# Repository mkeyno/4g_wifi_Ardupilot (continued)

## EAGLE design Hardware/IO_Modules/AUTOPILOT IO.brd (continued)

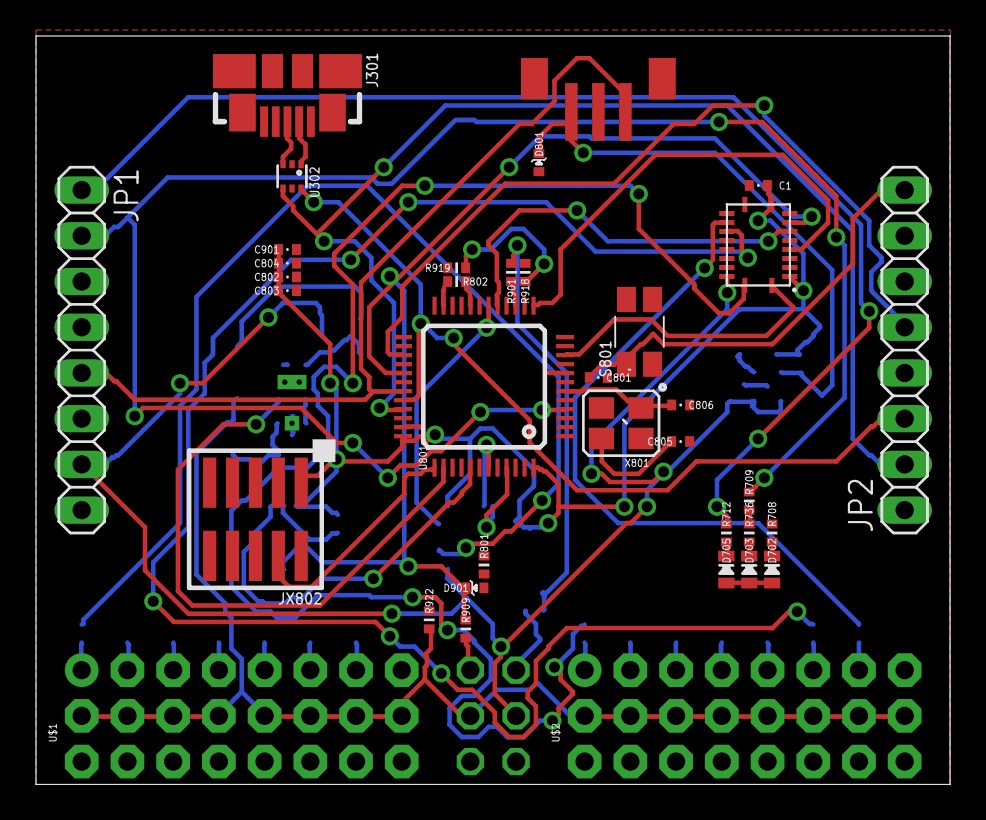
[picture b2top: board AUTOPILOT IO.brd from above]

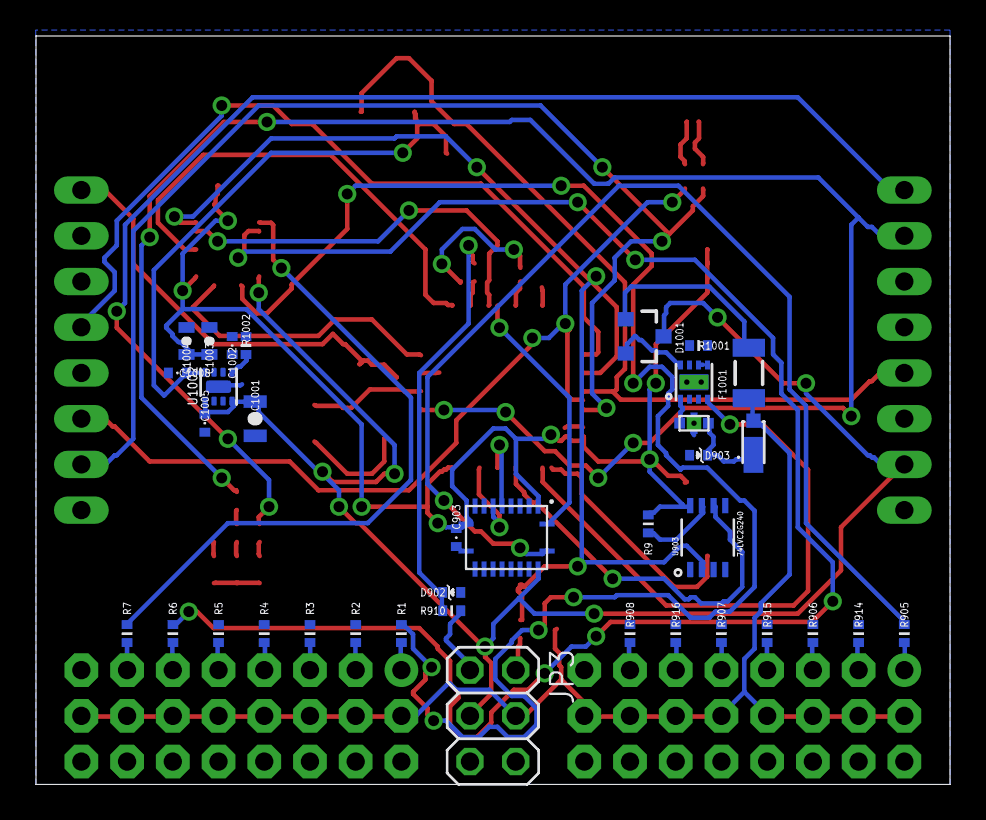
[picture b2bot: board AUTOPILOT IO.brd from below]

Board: 2 copper layers, 50.8 x 41.6 mm, 72 parts (36 on the bottom side), 91 nets.

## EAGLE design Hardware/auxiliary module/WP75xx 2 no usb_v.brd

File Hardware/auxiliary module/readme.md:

Airprime WPx5xx-76xx series is a Multiple-core embedded Linux system which used as  auxiliary core system that can provide secondary & backup IMU data, GPS data, advance terrain navigation , 4G video streaming and any hardware management for enhancing drone capabilities

## Specification  ##

In this 2 layer design following peripheral has been break out 
- 1 sync  Serial port
- 1 SPI(slave) 
- 1 I2C port
- 1 mini sim card slut 
- 1 USB 2.1 port
- 1 SD mini card slut 
- 4 analog pin

size of board is 7x5 cm

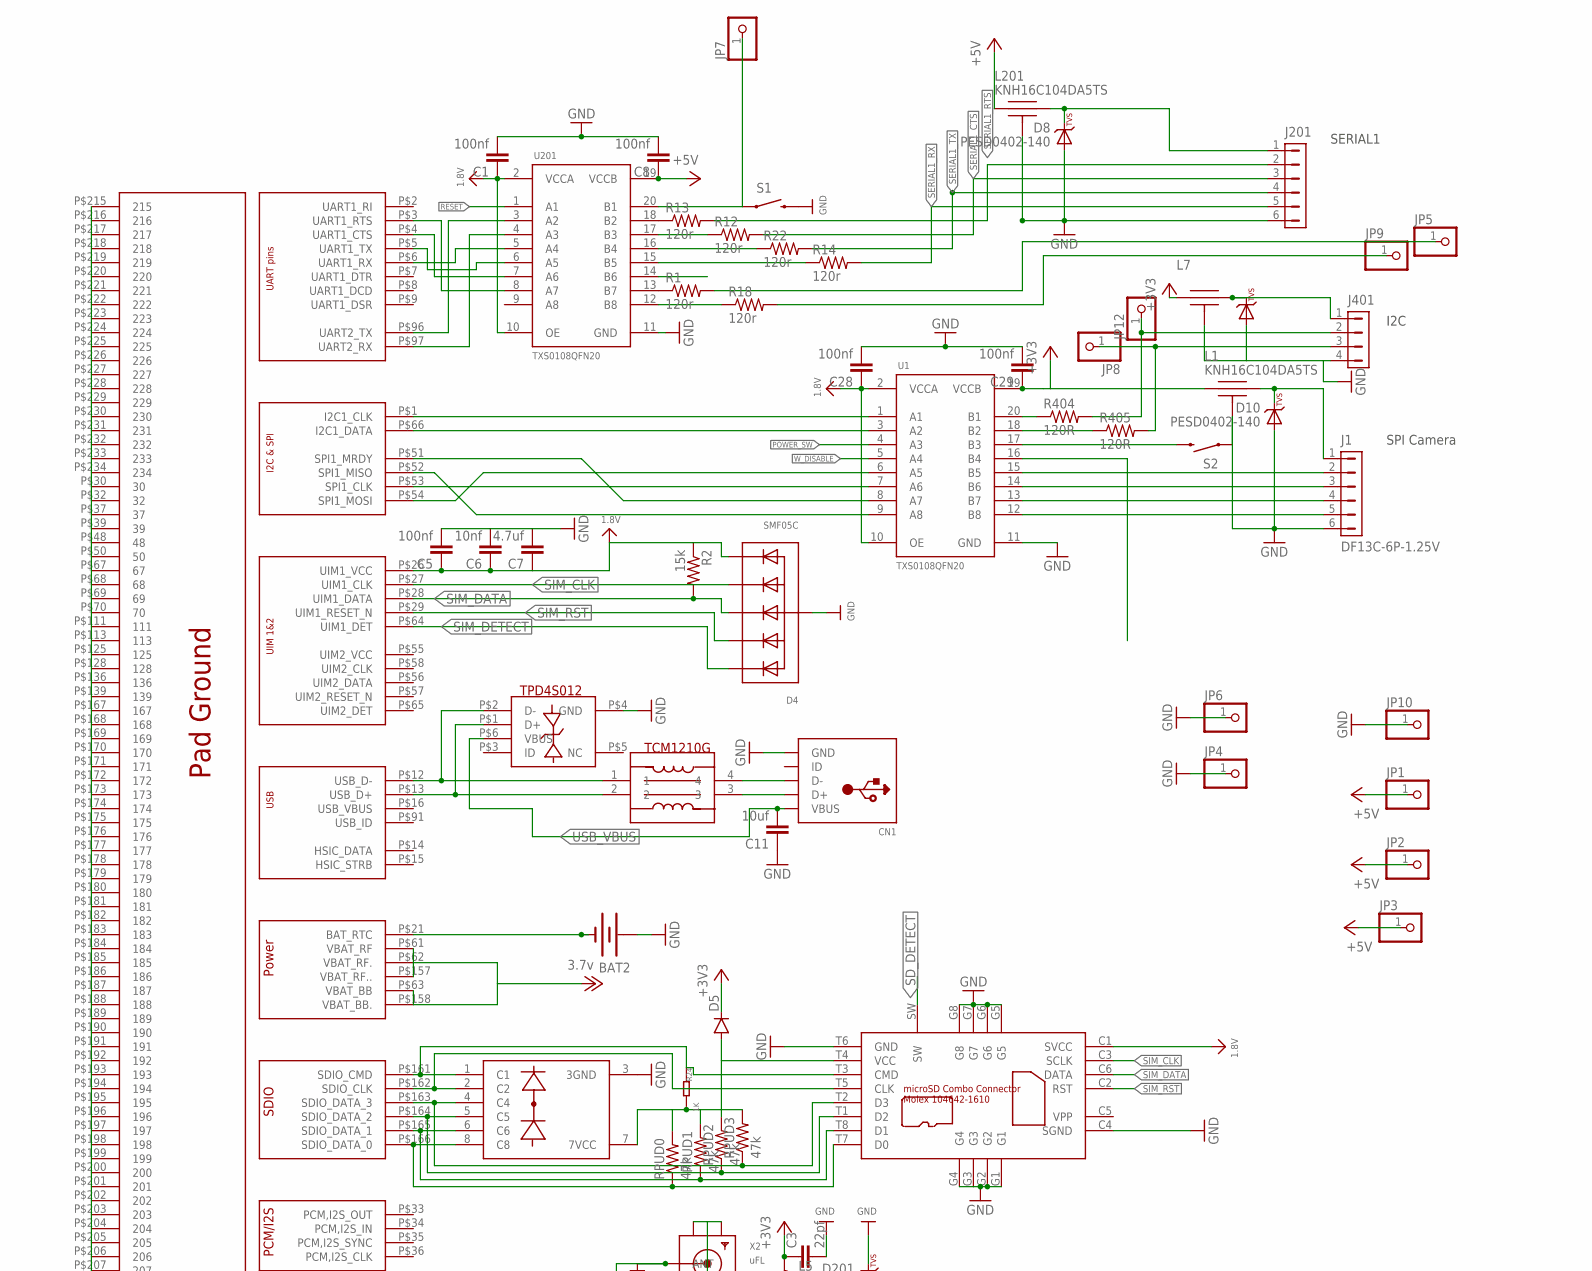
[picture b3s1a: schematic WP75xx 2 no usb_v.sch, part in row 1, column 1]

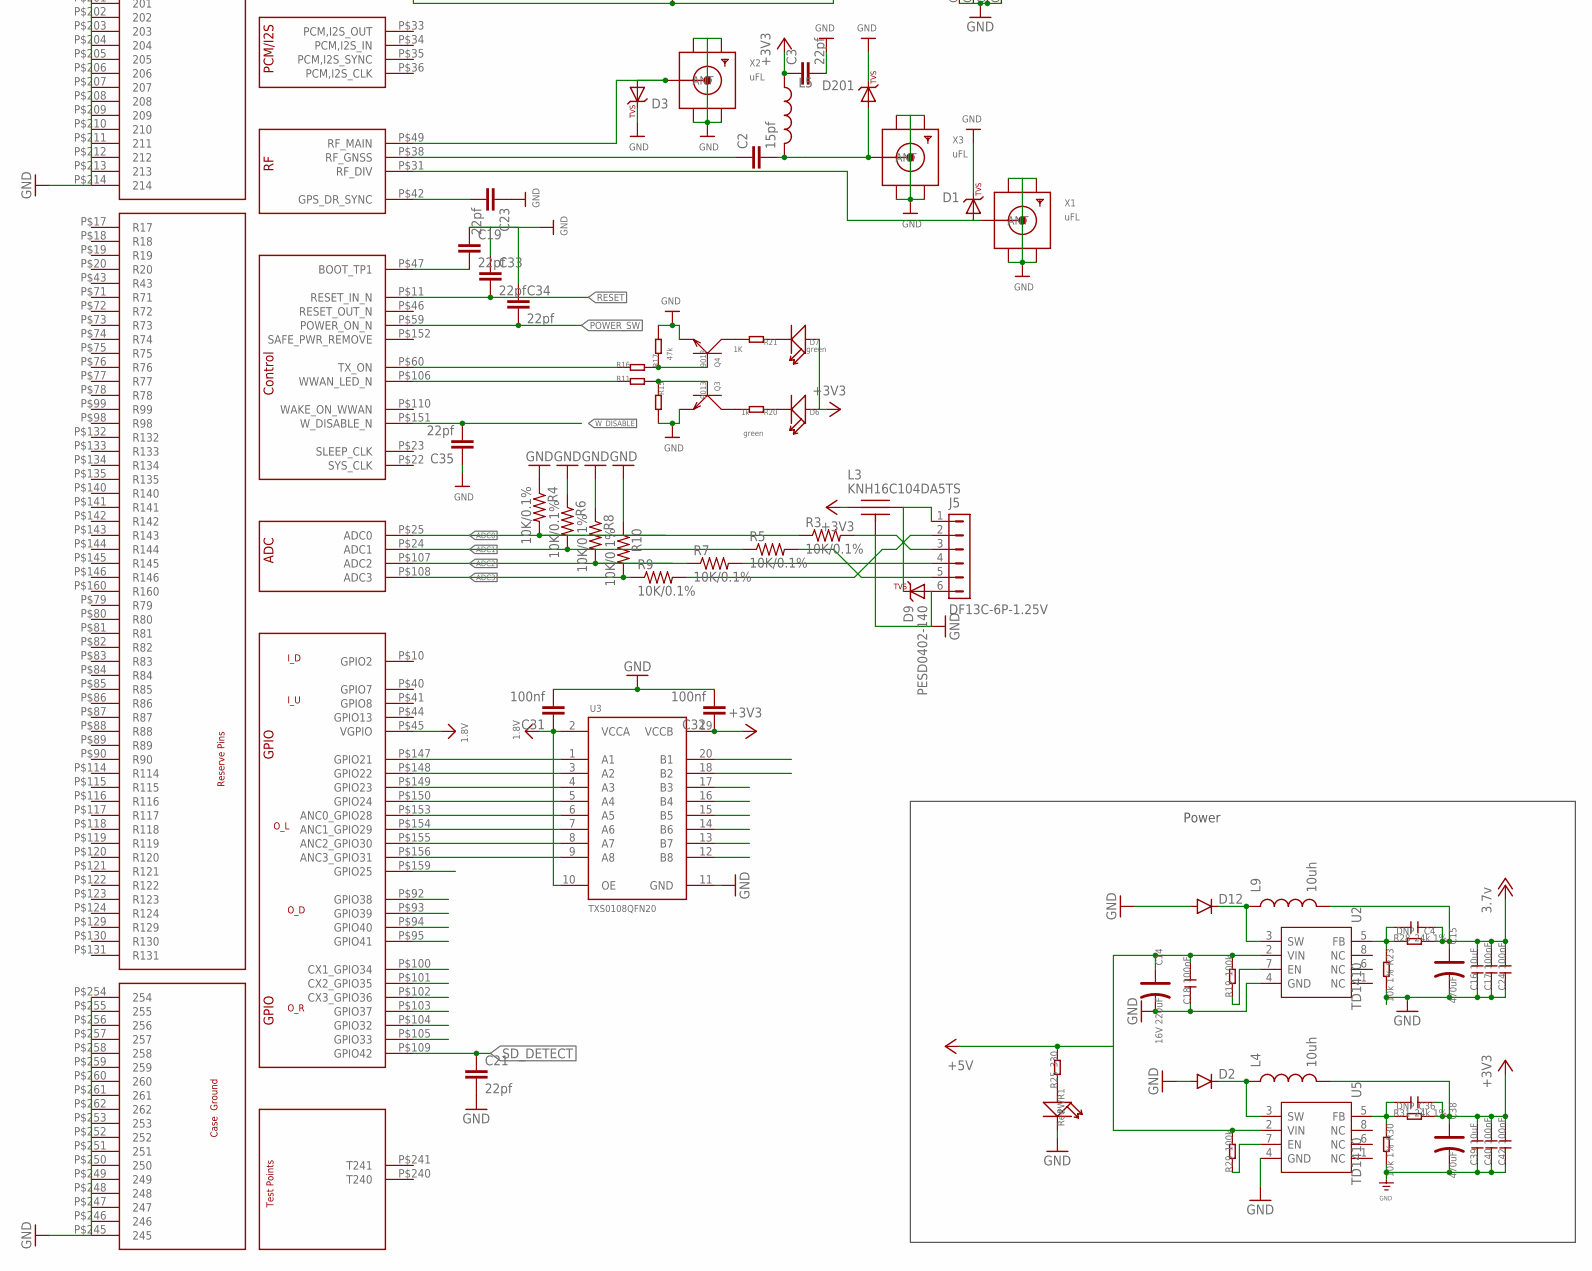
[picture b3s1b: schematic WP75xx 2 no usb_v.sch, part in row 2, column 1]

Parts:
BAT2: BATTERY12MM; BATTCON_12MM
C1, C5, C8, C28, C29, C31, C32: 100nf; 0805-CAP
C2: 15pf; 0603-CAP
C3, C19, C21, C23, C33, C34, C35: 22pf; 0603-CAP
C4, C36: DNP; C0603
C6: 10nf; 0805-CAP
C7: 4.7uf; 0805-CAP
C11: 10uf; 0603-CAP
C14: 16V 220uF; ELECTRO-SMD-D-5.6MM
C15, C38: 470uF; AVX-D
C16, C39: 10uF; C0805
C17, C18, C24, C40, C42: 100nF; C0603
CN1: USBMINIB; USB-MINIB
D1, D3, D201, D401: DIODE-TVS; 0402-TVS; PARTNO PESD0402-140
D2, D12: DIODESMA-KIT; SMA-DIODE-KIT
D4: SMF05C; SOT363
D5: DIODESOD123; SOD-123
D6, D7: green; LED-0603
D8, D9, D10: PESD0402-140; 0402-TVS; PARTNO PESD0402-140
J1, J5: DF13C-6P-1.25V; PARTNO DF13C-6P-1.25V(20)
J201: DF13-6P-1.25V; DF13C-6P-1.25V; PARTNO DF13C-6P-1.25V(20)
J401: DF13-4P-1.25V; DF13C-4P-1.25V; PARTNO DF13C-4P-1.25V(20)
JP1, JP2, JP3, JP4, JP5, JP6, JP7, JP8, JP9, JP10, JP12: PINHD-1X1; 1X01
L1, L3, L7, L201: KNH16C104DA5TS; KYOCERA-KNH16-DA; PARTNO KNH16C104DA5TS
L4, L9: 10uh; 1210
L5: INDUCTOR30OHM,1.8A; 0603
PWR1: Red; D0603
Q3, Q4: 9013; SOT23
R1, R12, R13, R14, R18, R22: 120r; 0603
R2: 15k; 0603
R3, R4, R5, R6, R7, R8, R9, R10: 10K/0.1%; 0402-RES; PARTNO ERA-2AEB103X
R11, R16: 4.7k; R0603
R15, R17: 47k; R0603
R19, R29: 100k; R0603
R20: 1k; R0603
R21, R24: 1K; R0603
R23, R30: 10k 1%; R0603
R25: 330; R0603
R28, R31: 24k 1%; R0603
R404, R405: 120R; 0402-RES; PARTNO RC0402FR-07120RL
RPUD0, RPUD1, RPUD2, RPUD3: 47k; 0603
S1, S2: SWITCH-MOMENTARY-2SMD-1101NE; TACTILE-SWITCH-1101NE
U1, U3, U201: TXS0108QFN20; QFN20-RGY; PARTNO TXS0108ERGYR
U2, U5: TD1410; SOP8
U$1: SOCKETY_WP75XXX; SOCKET_WP75XX
U$11: TCM1210G
U$12: TPD4S012
U$14: SD_SIM_M1610; SIM_SD_HOLDER
U$15: PACDN006; MSOP8
X1, X2, X3: uFL; SMA_EDGELAUNCH_UFL

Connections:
1.8V: C1.1, C5.1, C6.1, C7.1, C28.1, C31.1, D4.6 (C5), R2.1, U1.2 (VCCA), U1.10 (OE), U3.2 (VCCA), U3.10 (OE), U201.2 (VCCA), U201.10 (OE), U$1.P$26 (UIM1_VCC), U$1.P$45 (VGPIO), U$14.C1 (SVCC)
3.7V: C4.1, C15.+, C16.2, C17.2, C24.2, L9.2, R28.2, U$1.P$61 (VBAT_RF), U$1.P$62 (VBAT_RF.), U$1.P$63 (VBAT_BB), U$1.P$157 (VBAT_RF..), U$1.P$158 (VBAT_BB.)
21: U3.1 (A1), U$1.P$147 (GPIO21)
22: U3.3 (A2), U$1.P$148 (GPIO22)
23: U3.4 (A3), U$1.P$149 (GPIO23)
24: U3.5 (A4), U$1.P$150 (GPIO24)
28: U3.6 (A5), U$1.P$153 (ANC0_GPIO28)
29: U3.7 (A6), U$1.P$154 (ANC1_GPIO29)
30: U3.8 (A7), U$1.P$155 (ANC2_GPIO30)
31: U3.9 (A8), U$1.P$156 (ANC3_GPIO31)
+3V3: C3.1, C29.1, C32.1, C36.1, C38.+, C39.2, C40.2, C42.2, D5.C, D6.+, D7.+, L1.P$1, L3.P$1, L4.2, L5.1, L7.P$1, R31.2, U1.19 (VCCB), U3.19 (VCCB)
+5V: C8.1, C14.+, C18.2, JP1.1, JP2.1, JP3.1, L201.P$1, R19.2, R25.2, R29.2, U2.2 (VIN), U5.2 (VIN), U201.19 (VCCB)
ADC0: R3.P$1 (1), R4.P$2 (2), U$1.P$25 (ADC0)
ADC1: R5.P$1 (1), R6.P$2 (2), U$1.P$24 (ADC1)
ADC2: R7.P$1 (1), R8.P$2 (2), U$1.P$107 (ADC2)
ADC3: R9.P$1 (1), R10.P$2 (2), U$1.P$108 (ADC3)
BAT_RTC: BAT2.GND (-), U$1.P$21 (BAT_RTC)
BOOT_TPI: C19.2, U$1.P$47 (BOOT_TP1)
D+: U$1.P$13 (USB_D+), U$11.2, U$12.P$1 (D+)
D-: U$1.P$12 (USB_D-), U$11.1, U$12.P$2 (D-)
GND: BAT2.PWR@1 (+), C1.2, C3.2, C5.2, C6.2, C7.2, C8.2, C11.1, C14.-, C15.-, C16.1, C17.1, C18.1, C19.1, C21.2, C23.1, C24.1, C28.2, C29.2, C31.2, C32.2, C33.1, C34.1, C35.1, C38.-, C39.1, C40.1, C42.1, CN1.GND, D1.C, D2.A, D3.C, D4.2 (A), D8.A, D9.A, D10.A, D12.A, D201.C, D401.A, J1.6, J5.6, J201.6, J401.4, JP4.1, JP6.1, JP10.1, L1.P$3, L1.P$4, L1.P$5, L3.P$3, L3.P$4, L3.P$5, L7.P$3, L7.P$4, L7.P$5, L201.P$3, L201.P$4, L201.P$5, PWR1.-, Q3.2 (E), Q4.2 (E), R4.P$1 (1), R6.P$1 (1), R8.P$1 (1), R10.P$1 (1), R15.2, R17.2, R23.2, R30.2, S1.2, S2.1, U1.11 (GND), U2.4 (GND), U3.11 (GND), U5.4 (GND), U201.11 (GND), U$1.P$30 (30), U$1.P$32 (32), U$1.P$37 (37), U$1.P$39 (39), U$1.P$48 (48), U$1.P$50 (50), U$1.P$67 (67), U$1.P$68 (68), U$1.P$69 (69), U$1.P$70 (70), U$1.P$111 (111), U$1.P$113 (113), U$1.P$125 (125), U$1.P$128 (128), U$1.P$136 (136), U$1.P$139 (139), U$1.P$167 (167), U$1.P$168 (168), U$1.P$169 (169), U$1.P$170 (170), U$1.P$171 (171), U$1.P$172 (172), U$1.P$173 (173), U$1.P$174 (174), U$1.P$175 (175), U$1.P$176 (176), U$1.P$177 (177), U$1.P$178 (178), U$1.P$179 (179), U$1.P$180 (180), U$1.P$181 (181), U$1.P$182 (182), U$1.P$183 (183), U$1.P$184 (184), U$1.P$185 (185), U$1.P$186 (186), U$1.P$187 (187), U$1.P$188 (188), U$1.P$189 (189), U$1.P$190 (190), U$1.P$191 (191), U$1.P$192 (192), U$1.P$193 (193), U$1.P$194 (194), U$1.P$195 (195), U$1.P$196 (196), U$1.P$197 (197), U$1.P$198 (198), U$1.P$199 (199), U$1.P$200 (200), U$1.P$201 (201), U$1.P$202 (202), U$1.P$203 (203), U$1.P$204 (204), U$1.P$205 (205), U$1.P$206 (206), U$1.P$207 (207), U$1.P$208 (208), U$1.P$209 (209), U$1.P$210 (210), U$1.P$211 (211), U$1.P$212 (212), U$1.P$213 (213), U$1.P$214 (214), U$1.P$215 (215), U$1.P$216 (216), U$1.P$217 (217), U$1.P$218 (218), U$1.P$219 (219), U$1.P$220 (220), U$1.P$221 (221), U$1.P$222 (222), U$1.P$223 (223), U$1.P$224 (224), U$1.P$225 (225), U$1.P$226 (226), U$1.P$227 (227), U$1.P$228 (228), U$1.P$229 (229), U$1.P$230 (230), U$1.P$231 (231), U$1.P$232 (232), U$1.P$233 (233), U$1.P$234 (234), U$1.P$245 (245), U$1.P$246 (246), U$1.P$247 (247), U$1.P$248 (248), U$1.P$249 (249), U$1.P$250 (250), U$1.P$251 (251), U$1.P$252 (252), U$1.P$253 (253), U$1.P$254 (254), U$1.P$255 (255), U$1.P$256 (256), U$1.P$257 (257), U$1.P$258 (258), U$1.P$259 (259), U$1.P$260 (260), U$1.P$261 (261), U$1.P$262 (262), U$12.P$4 (GND), U$14.C4 (SGND), U$14.G1, U$14.G2, U$14.G3, U$14.G4, U$14.G5, U$14.G6, U$14.G7, U$14.G8, U$14.T6 (GND), U$15.3 (3GND), X1.GND@1 (GND1), X1.GND@2 (GND2), X1.GND@3 (GND3), X1.GND@4 (GND4), X2.GND@1 (GND1), X2.GND@2 (GND2), X2.GND@3 (GND3), X2.GND@4 (GND4), X3.GND@1 (GND1), X3.GND@2 (GND2), X3.GND@3 (GND3), X3.GND@4 (GND4)
GPS_ANT: C2.1, U$1.P$38 (RF_GNSS)
GPS_SYNC: C23.2, U$1.P$42 (GPS_DR_SYNC)
MAIN_ANT: D3.A, U$1.P$49 (RF_MAIN), X2.P (ANT)
unnamed: D9.C, J5.1, L3.P$2
unnamed: CN1.D+, U$11.3
unnamed: D5.A, R24.2, RPUD0.2, RPUD1.2, RPUD2.2, RPUD3.2, U$14.T4 (VCC), U$15.7 (7VCC)
unnamed: C2.2, D201.A, L5.2, X3.P (ANT)
unnamed: J401.2, JP12.1, R404.P$2 (2)
unnamed: R24.1, U$1.P$161 (SDIO_CMD), U$14.T3 (CMD), U$15.1 (C1)
unnamed: U$1.P$162 (SDIO_CLK), U$14.T5 (CLK), U$15.2 (C2)
unnamed: RPUD3.1, U$1.P$163 (SDIO_DATA_3), U$14.T2 (D3), U$15.4 (C4)
unnamed: RPUD2.1, U$1.P$164 (SDIO_DATA_2), U$14.T1 (D2), U$15.5 (C5)
unnamed: CN1.D-, U$11.4
unnamed: RPUD1.1, U$1.P$165 (SDIO_DATA_1), U$14.T8 (D1), U$15.6 (C6)
unnamed: RPUD0.1, U$1.P$166 (SDIO_DATA_0), U$14.T7 (D0), U$15.8 (C8)
unnamed: D10.C, J1.1, L1.P$2
unnamed: J5.5, R5.P$2 (2)
unnamed: J5.3, R3.P$2 (2)
unnamed: J5.4, R7.P$2 (2)
unnamed: D8.C, J201.1, L201.P$2
unnamed: Q3.3 (C), R20.2
unnamed: R22.1, U201.16 (B4)
unnamed: R12.1, U201.17 (B3)
unnamed: R13.1, U201.18 (B2)
unnamed: J5.2, R9.P$2 (2)
unnamed: R14.1, U201.15 (B5)
unnamed: U1.6 (A5), U$1.P$54 (SPI1_MOSI)
unnamed: U1.7 (A6), U$1.P$53 (SPI1_CLK)
unnamed: U1.9 (A8), U$1.P$52 (SPI1_MISO)
unnamed: U1.8 (A7), U$1.P$51 (SPI1_MRDY)
unnamed: U201.8 (A7), U$1.P$3 (UART1_RTS)
unnamed: J1.5, U1.12 (B8)
unnamed: S2.2, U1.17 (B3)
unnamed: J1.4, U1.13 (B7)
unnamed: J1.3, U1.14 (B6)
unnamed: J1.2, U1.15 (B5)
unnamed: U201.5 (A4), U$1.P$6 (UART1_RX)
unnamed: U201.6 (A5), U$1.P$5 (UART1_TX)
unnamed: U201.7 (A6), U$1.P$4 (UART1_CTS)
unnamed: PWR1.+, R25.1
unnamed: JP7.1, S1.1, U201.20 (B1)
unnamed: D6.-, R20.1
unnamed: Q3.1 (B), R11.2, R15.1
unnamed: Q4.3 (C), R21.2
unnamed: D7.-, R21.1
unnamed: Q4.1 (B), R16.2, R17.1
unnamed: R19.1, U2.7 (EN)
unnamed: D401.C, J401.1, L7.P$2
unnamed: D12.C, L9.1, U2.3 (SW)
unnamed: R404.P$1 (1), U1.20 (B1)
unnamed: R405.P$1 (1), U1.18 (B2)
unnamed: R1.1, U201.13 (B7)
unnamed: R18.1, U201.12 (B8)
unnamed: JP5.1, R1.2
unnamed: C4.2, R23.1, R28.1, U2.5 (FB)
unnamed: R29.1, U5.7 (EN)
unnamed: D2.C, L4.1, U5.3 (SW)
unnamed: C36.2, R30.1, R31.1, U5.5 (FB)
unnamed: JP9.1, R18.2
unnamed: J401.3, JP8.1, R405.P$2 (2)
POWER_SW: C34.2, U1.4 (A3), U$1.P$59 (POWER_ON_N)
RESET: C33.2, U201.1 (A1), U$1.P$11 (RESET_IN_N)
RF_DIV: D1.A, U$1.P$31 (RF_DIV), X1.P (ANT)
RX2: U201.4 (A3), U$1.P$97 (UART2_RX)
SCL: U1.1 (A1), U$1.P$1 (I2C1_CLK)
SDA: U1.3 (A2), U$1.P$66 (I2C1_DATA)
SD_DETECT: C21.1, U$1.P$109 (GPIO42), U$14.SW
SERIAL1_CTS: J201.3, R12.2
SERIAL1_RTS: J201.2, R13.2
SERIAL1_RX: J201.5, R14.2
SERIAL1_TX: J201.4, R22.2
SIM_CLK: D4.5 (C4), U$1.P$27 (UIM1_CLK), U$14.C3 (SCLK)
SIM_DATA: D4.4 (C3), R2.2, U$1.P$28 (UIM1_DATA), U$14.C6 (DATA)
SIM_DETECT: D4.1 (C1), U$1.P$64 (UIM1_DET)
SIM_RST: D4.3 (C2), U$1.P$29 (UIM1_RESET_N), U$14.C2 (RST)
TX2: U201.3 (A2), U$1.P$96 (UART2_TX)
TX_ACTIVITY: R16.1, U$1.P$60 (TX_ON)
USB_VBUS: C11.2, CN1.VBUS, U$12.P$6 (VBUS)
WAN_LED: R11.1, U$1.P$106 (WWAN_LED_N)
W_DISABLE: C35.2, U1.5 (A4), U$1.P$151 (W_DISABLE_N)

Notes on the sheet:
SERIAL1
SPI Camera
Power
I2C

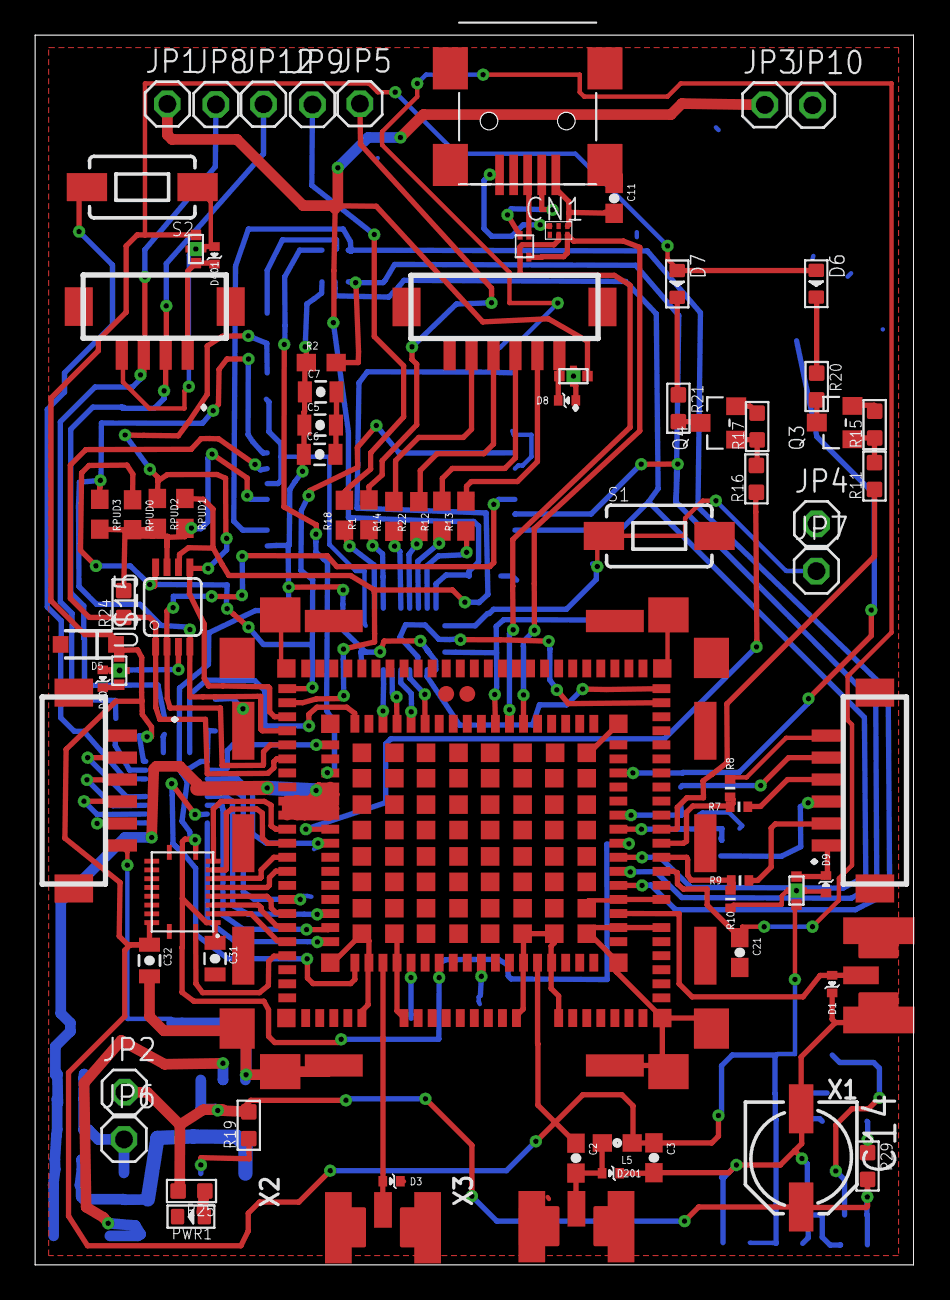
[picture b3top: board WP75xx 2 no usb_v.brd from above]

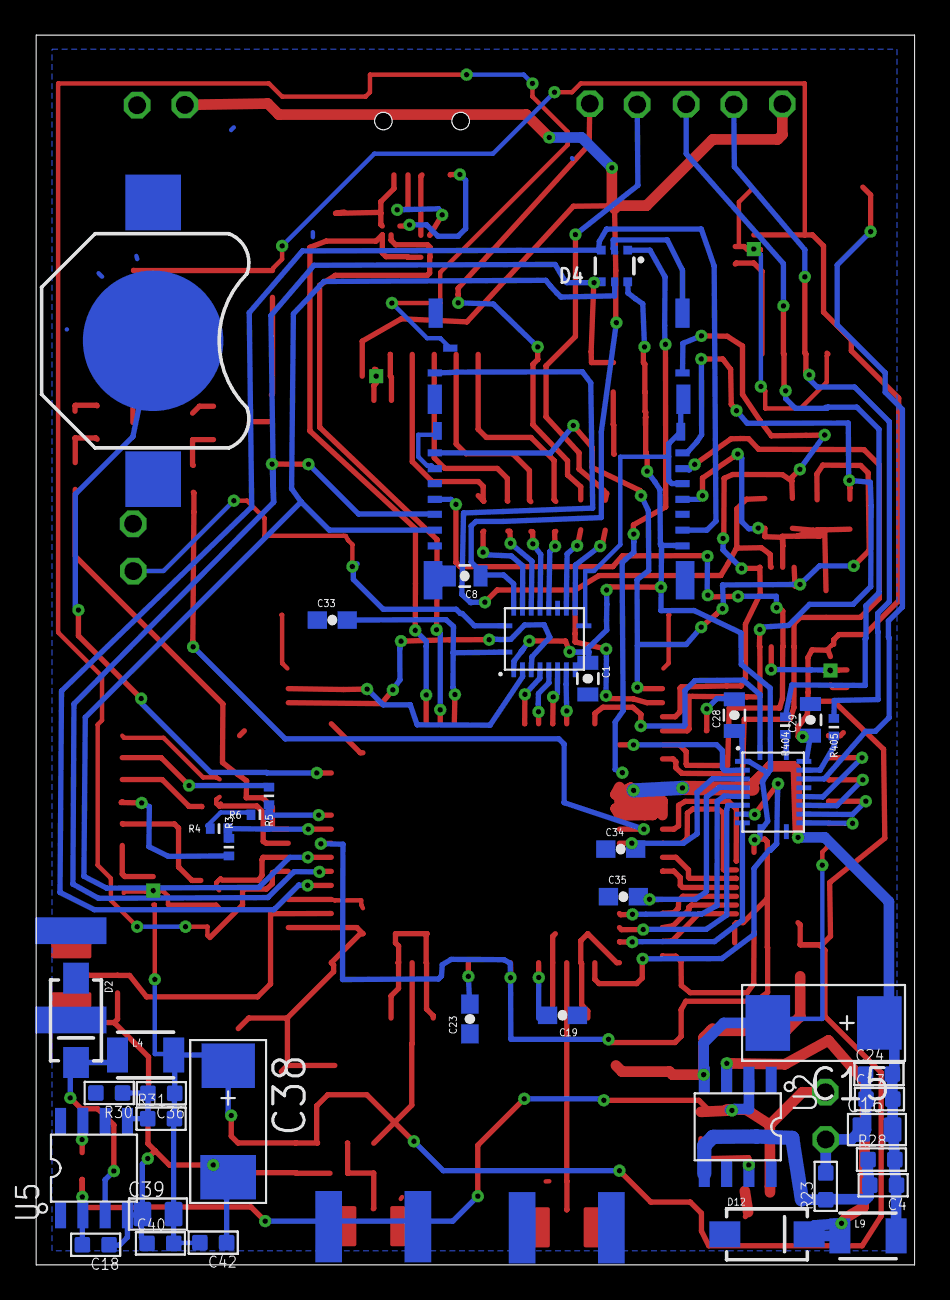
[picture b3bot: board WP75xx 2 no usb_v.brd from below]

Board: 2 copper layers, 50.0 x 70.0 mm, 120 parts (41 on the bottom side), 101 nets.

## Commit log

2018-08-25 create preface
    create readme
2018-08-25 Create hardware
2018-08-25 Create Images
2018-10-28 photos
2018-12-14 Add files via upload
    AC_AttitudeControl library
2018-12-14 Add files via upload
    AC_Avoidance lib
2018-12-14 Add files via upload
    AC_Fence lib
2018-12-14 Add files via upload
    AC_InputManager lib
2018-12-26 Add files via upload
    AC WPNav
